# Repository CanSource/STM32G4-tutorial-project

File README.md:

# kicad project STM32G4-tutorial-project

a cool table showing the workflow of all the kicad projects.
| project_name | DRC | ERC |
| ------------ | --- | --- |
| stm32-tutorial-project | [❌](https://github.com/CanSource/STM32G4-tutorial-project/actions/runs/15577171902/attempts/1#summary-43864188891)| [❌](https://github.com/CanSource/STM32G4-tutorial-project/actions/runs/15577171902/attempts/1#summary-43864188888) | 

for a quick guide check [project setup](#project-setup)

This is a simple project template for new kicad projects. This template has some basic setup already completed such as workflows for auto creating all the things you forget when creating a kicad project such as:

- [gerbers](https://github.com/CanSource/STM32G4-tutorial-project/tree/main/stm32-tutorial-project_gerber.zip)
- [bom](https://github.com/CanSource/STM32G4-tutorial-project/tree/main/stm32-tutorial-project_bom_report.md)
- [schematic pdf](https://github.com/CanSource/STM32G4-tutorial-project/tree/main/stm32-tutorial-project_schematic.pdf)

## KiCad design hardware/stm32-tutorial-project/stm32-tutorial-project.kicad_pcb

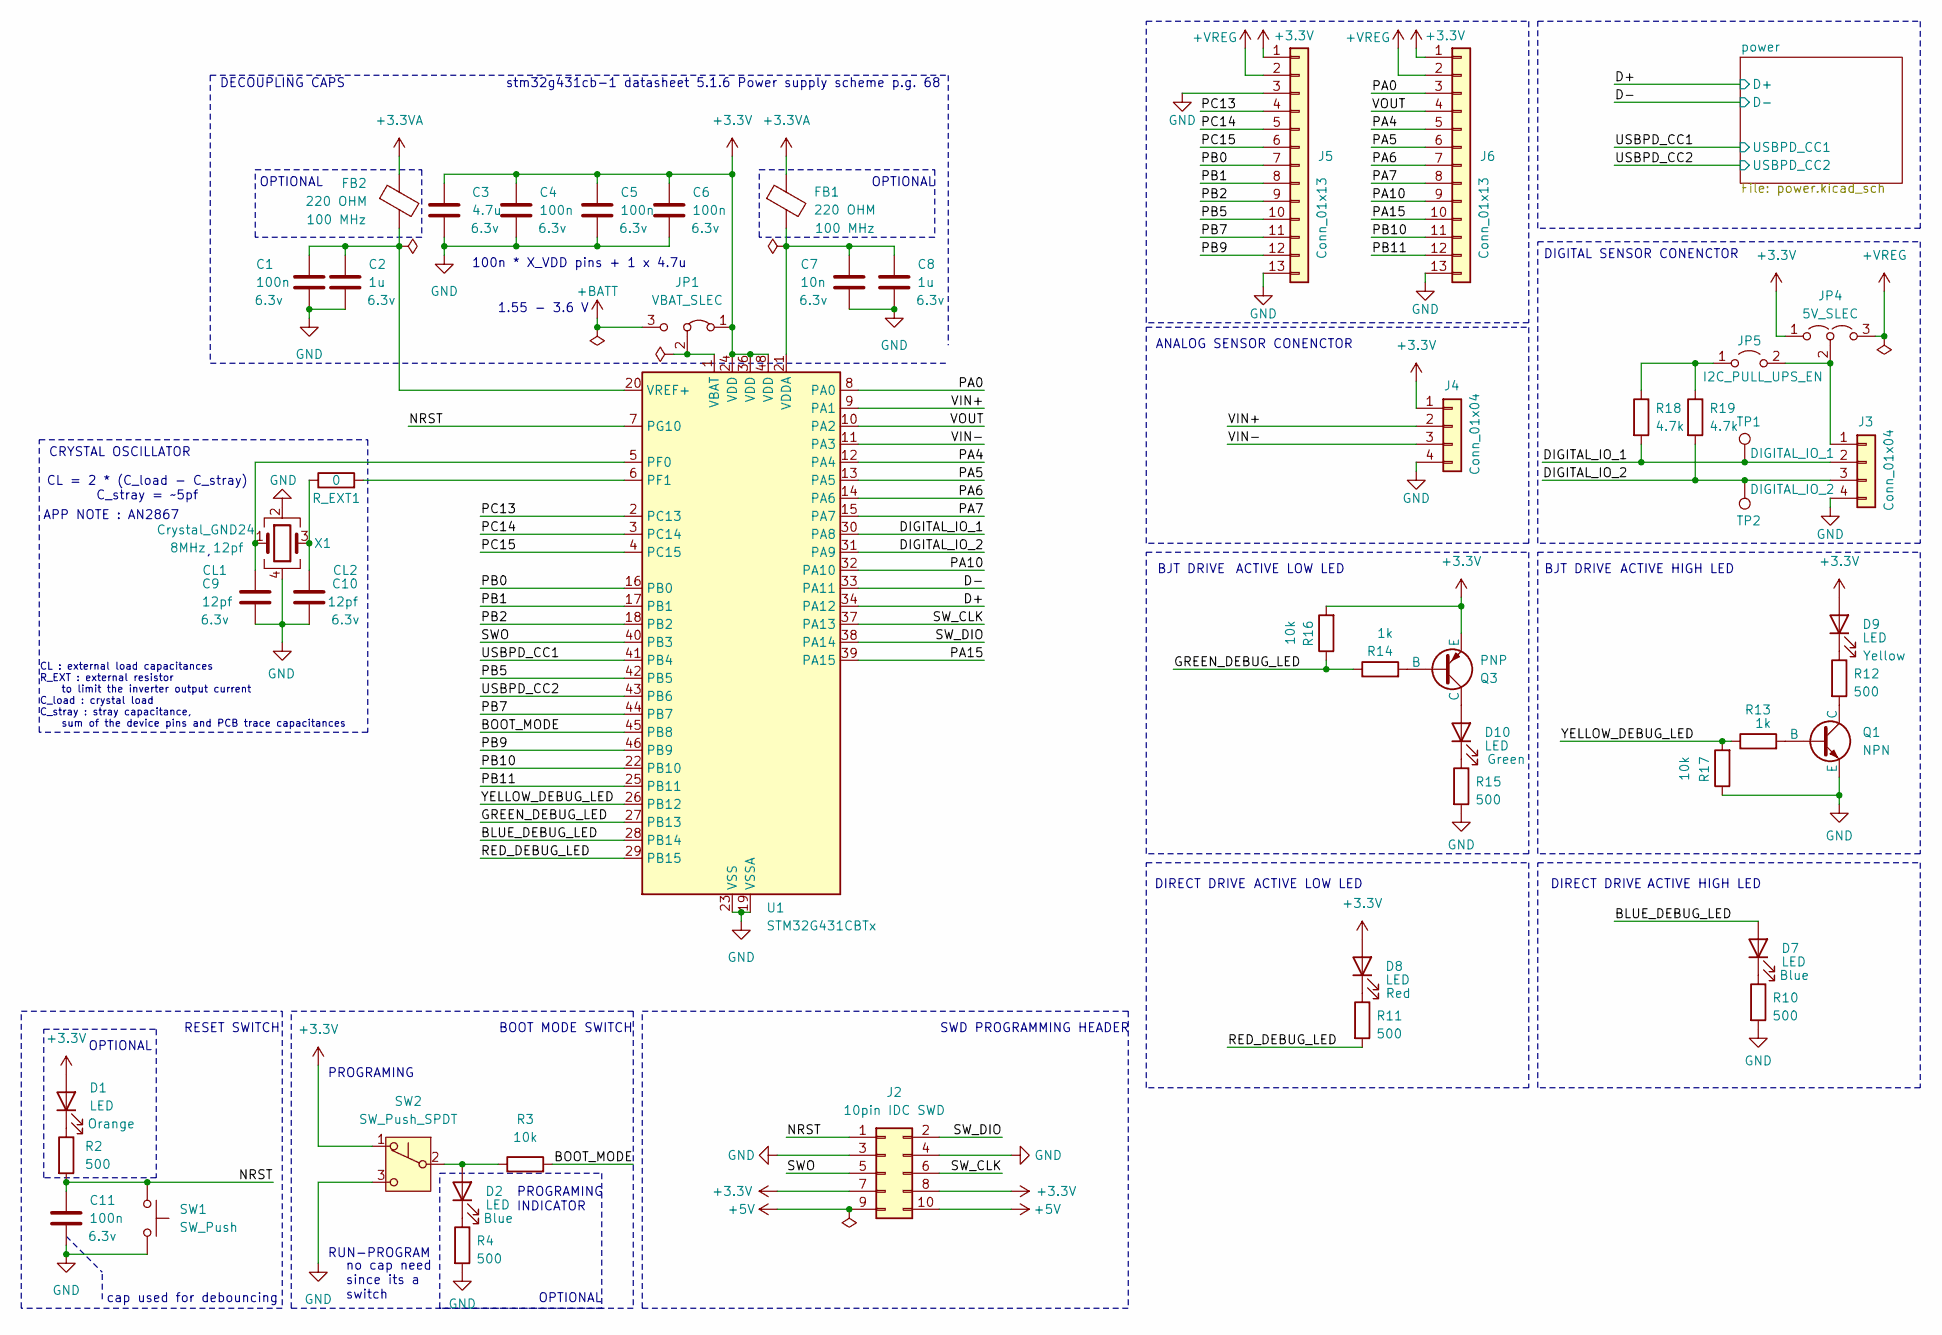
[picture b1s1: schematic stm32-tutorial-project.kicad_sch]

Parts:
C1: 100n; C_0603_1608Metric_Pad1.08x0.95mm_HandSolder; voltage 6.3v; rating X7R; Part Number C0603C104K9RACTU
C2, C8: 1u; C_0603_1608Metric_Pad1.08x0.95mm_HandSolder; voltage 6.3v; rating X7R; Part Number C0603C105K9RACTU
C3: 4.7u; C_0603_1608Metric_Pad1.08x0.95mm_HandSolder; voltage 6.3v; rating X5R; Part Number C0603C475K9PACTU
C4, C5, C6, C11: 100n; C_0603_1608Metric_Pad1.08x0.95mm_HandSolder; voltage 6.3v; rating X5R; Part Number C0603C104K9PACTU
C7: 10n; C_0603_1608Metric_Pad1.08x0.95mm_HandSolder; voltage 6.3v; rating X7R; Part Number C0603C103K9RACTU
C9, C10: 12pf; C_0603_1608Metric_Pad1.08x0.95mm_HandSolder; voltage 6.3v; rating X7R; Part Number C0603C120K9RAC7411
D1: LED; D_0603_1608Metric_Pad1.05x0.95mm_HandSolder; Part Number 150060AS75000
D2, D7: LED; D_0603_1608Metric_Pad1.05x0.95mm_HandSolder; Part Number 150060BS75000
D8: LED; D_0603_1608Metric_Pad1.05x0.95mm_HandSolder; Part Number 150060RS75000
D9: LED; D_0603_1608Metric_Pad1.05x0.95mm_HandSolder; Part Number 150060YS75000
D10: LED; D_0603_1608Metric_Pad1.05x0.95mm_HandSolder; Part Number 150060VS75000
FB1, FB2: 220 OHM; L_0603_1608Metric_Pad1.05x0.95mm_HandSolder; Part Number MH1608-221Y
J2: 10pin IDC SWD; IDC-Header_2x05_P2.54mm_Vertical; Part Number AWHW2 10G-0202
J3, J4: Conn_01x04; PinHeader_1x04_P2.54mm_Vertical; Part Number 1-0401FBV0T
J5, J6: Conn_01x13; PinHeader_1x13_P2.54mm_Vertical
JP1: VBAT_SLEC; SolderJumper-3_P1.3mm_Open_Pad1.0x1.5mm_NumberLabels
JP4: 5V_SLEC; PinHeader_1x03_P2.54mm_Vertical
JP5: I2C_PULL_UPS_EN; PinHeader_1x02_P2.54mm_Vertical
Q1: NPN; TSOT-23_HandSoldering; Part Number MMBT3904
Q3: PNP; TSOT-23_HandSoldering; Part Number MMBT3906
R2, R4, R10, R11, R12, R15: 500; R_0603_1608Metric_Pad0.98x0.95mm_HandSolder; Part Number RT0603BRD07500RL
R3, R16, R17: 10k; R_0603_1608Metric_Pad0.98x0.95mm_HandSolder; Part Number RC0603FR-0710KL
R13, R14: 1k; R_0603_1608Metric_Pad0.98x0.95mm_HandSolder; Part Number RC0603FR-0710KL
R18, R19: 4.7k; R_0603_1608Metric_Pad0.98x0.95mm_HandSolder; Part Number RC0603FR-074K7L
R_EXT1: 0; R_0603_1608Metric_Pad0.98x0.95mm_HandSolder; Part Number RC0603JR-070RL
SW1: SW_Push; SW_Tactile_SPST_NO_Straight_CK_PTS636Sx25SMTRLFS; Part Number PTS636SM43SMTR LFS
SW2: SW_Push_SPDT; SW_Slide_SPDT_Angled_CK_OS102011MA1Q; Part Number OS102011MA1QN1
TP1: DIGITAL_IO_1; TestPoint_Pad_D3.0mm
TP2: DIGITAL_IO_2; TestPoint_Pad_D3.0mm
U1: STM32G431CBTx; LQFP-48_7x7mm_P0.5mm; Part Number STM32G431CBT6
X1: Crystal_GND24; Crystal_SMD_3225-4Pin_3.2x2.5mm_HandSoldering; Part Number 12.60049

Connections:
+3.3V: C3.1, C4.1, C5.1, C6.1, D1.2 (A), D8.2 (A), D9.2 (A), FB1.1, FB2.1, J2.7, J2.8, J4.1, J5.1, J6.1, JP1.1 (A), JP4.1 (A), Q3.3 (E), R16.2, SW2.1 (A), U1.24 (VDD), U1.36 (VDD), U1.48 (VDD); also elsewhere on the board
+5V: J2.9, J2.10; also elsewhere on the board
+BATT: JP1.3 (B)
+VREG: J5.2, J6.2, JP4.3 (B); also elsewhere on the board
/BLUE_DEBUG_LED: D7.2 (A), U1.28 (PB14)
/BOOT_MODE: R3.2, U1.45 (PB8)
/D+: U1.34 (PA12); also elsewhere on the board
/D-: U1.33 (PA11); also elsewhere on the board
/DIGITAL_IO_1: J3.2, R18.2, TP1.1, U1.30 (PA8)
/DIGITAL_IO_2: J3.3, R19.2, TP2.1, U1.31 (PA9)
/GREEN_DEBUG_LED: R14.1, R16.1, U1.27 (PB13)
/NRST: C11.1, J2.1, R2.2, SW1.1, U1.7 (PG10)
/PA0: J6.3, U1.8 (PA0)
/PA4: J6.5, U1.12 (PA4)
/PA5: J6.6, U1.13 (PA5)
/PA6: J6.7, U1.14 (PA6)
/PA7: J6.8, U1.15 (PA7)
/PA10: J6.9, U1.32 (PA10)
/PA15: J6.10, U1.39 (PA15)
/PB0: J5.7, U1.16 (PB0)
/PB1: J5.8, U1.17 (PB1)
/PB2: J5.9, U1.18 (PB2)
/PB5: J5.10, U1.42 (PB5)
/PB7: J5.11, U1.44 (PB7)
/PB9: J5.12, U1.46 (PB9)
/PB10: J6.11, U1.22 (PB10)
/PB11: J6.12, U1.25 (PB11)
/PC13: J5.4, U1.2 (PC13)
/PC14: J5.5, U1.3 (PC14)
/PC15: J5.6, U1.4 (PC15)
/RED_DEBUG_LED: R11.2, U1.29 (PB15)
/SWO: J2.5, U1.40 (PB3)
/SW_CLK: J2.6, U1.37 (PA13)
/SW_DIO: J2.2, U1.38 (PA14)
/USBPD_CC1: U1.41 (PB4); also elsewhere on the board
/USBPD_CC2: U1.43 (PB6); also elsewhere on the board
/VIN+: J4.2, U1.9 (PA1)
/VIN-: J4.3, U1.11 (PA3)
/VOUT: J6.4, U1.10 (PA2)
/YELLOW_DEBUG_LED: R13.1, R17.2, U1.26 (PB12)
GND: C1.2, C2.2, C3.2, C4.2, C5.2, C6.2, C7.2, C8.2, C9.2, C10.1, C11.2, J2.3, J2.4, J3.4, J4.4, J5.3, J5.13, J6.13, Q1.3 (E), R4.2, R10.2, R15.2, R17.1, SW1.2, SW2.3 (C), U1.19 (VSSA), U1.23 (VSS), U1.35 (VSS), U1.47 (VSS), X1.2, X1.4; also elsewhere on the board
unnamed: C10.2, R_EXT1.1, X1.3
unnamed: D1.1 (K), R2.1
unnamed: D2.2 (A), R3.1, SW2.2 (B)
unnamed: D2.1 (K), R4.1
unnamed: D7.1 (K), R10.1
unnamed: D8.1 (K), R11.1
unnamed: D9.1 (K), R12.1
unnamed: D10.2 (A), Q3.1 (C)
unnamed: D10.1 (K), R15.1
unnamed: J3.1, JP4.2 (C), JP5.2 (B)
unnamed: JP1.2 (C), U1.1 (VBAT)
unnamed: JP5.1 (A), R18.1, R19.1
unnamed: Q1.2 (B), R13.2
unnamed: Q1.1 (C), R12.2
unnamed: Q3.2 (B), R14.2
unnamed: C9.1, U1.5 (PF0), X1.1
unnamed: R_EXT1.2, U1.6 (PF1)
unnamed: C7.1, C8.1, FB1.2, U1.21 (VDDA)
unnamed: C1.1, C2.1, FB2.2, U1.20 (VREF+)

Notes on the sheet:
DIGITAL SENSOR CONENCTOR
APP NOTE : AN2867
no cap need since its a switch
CRYSTAL OSCILLATOR
DECOUPLING CAPS
ACTIVE LOW LED
100n * X_VDD pins + 1 x 4.7u
cap used for debouncing
PROGRAMING INDICATOR
stm32g431cb-1 datasheet 5.1.6 Power supply scheme p.g. 68
RESET SWITCH
BJT DRIVE
ACTIVE HIGH LED
ANALOG SENSOR CONENCTOR
PROGRAMING
DIRECT DRIVE
OPTIONAL
1.55 - 3.6 V
RUN-PROGRAM
CL : external load capacitances R_EXT : external resistor to limit the inverter output current C_load : crystal load C_stray : stray capacitance, sum of the device pins and PCB trace capacitances
CL = 2 * (C_load - C_stray) C_stray = ~5pf
BOOT MODE SWITCH
SWD PROGRAMMING HEADER

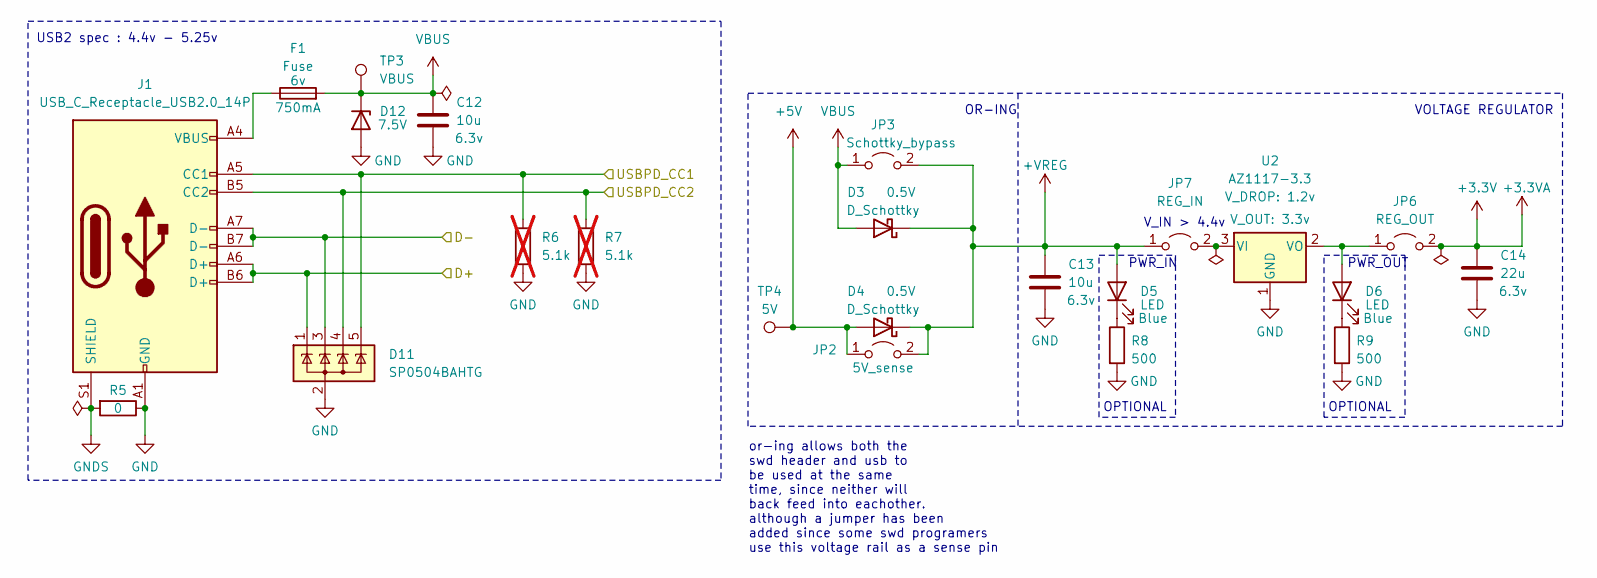
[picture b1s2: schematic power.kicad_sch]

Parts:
C12, C13: 10u; C_0603_1608Metric_Pad1.08x0.95mm_HandSolder; voltage 6.3v; rating X5R; Part Number C0603C106M9PACTU
C14: 22u; C_0603_1608Metric_Pad1.08x0.95mm_HandSolder; voltage 6.3v; rating X5R; Part Number C0805C226M9PACTU
D3, D4: D_Schottky; D_0603_1608Metric_Pad1.05x0.95mm_HandSolder; Part Number SD0805S020S1R0
D5, D6: LED; D_0603_1608Metric_Pad1.05x0.95mm_HandSolder; Part Number 150060BS75000
D11: SP0504BAHTG; SOT-23-5; Part Number SP0504BAHTG
D12: PTVS7V5Z1USK; Nexperia_DSN1608-2_1.6x0.8mm; Part Number PTVS7V5Z1USKYL
F1: Fuse; Fuse_0805_2012Metric; voltage 6v; Part Number 0ZCK0075FF2E
J1: USB_C_Receptacle_USB2.0_14P; USB_C_Receptacle_HRO_TYPE-C-31-M-12; Part Number USB4105-GF-A
JP2: 5V_sense; SolderJumper-2_P1.3mm_Open_Pad1.0x1.5mm
JP3: Schottky_bypass; SolderJumper-2_P1.3mm_Open_Pad1.0x1.5mm
JP6: REG_OUT; SolderJumper-2_P1.3mm_Open_Pad1.0x1.5mm
JP7: REG_IN; SolderJumper-2_P1.3mm_Open_Pad1.0x1.5mm
R5: 0; R_0603_1608Metric_Pad0.98x0.95mm_HandSolder; Part Number RC0603JR-070RL
R6, R7: 5.1k; R_0603_1608Metric_Pad0.98x0.95mm_HandSolder; Part Number RC0603FR-075K1L; not fitted
R8, R9: 500; R_0603_1608Metric_Pad0.98x0.95mm_HandSolder; Part Number RT0603BRD07500RL
TP3: VBUS; TestPoint_Pad_D3.0mm
TP4: 5V; TestPoint_Pad_D3.0mm
U2: AZ1117-3.3; SOT-223-3_TabPin2; Part Number AZ1117CH-3.3TRG1

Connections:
+3.3V: C14.1, JP6.2 (B); also elsewhere on the board
+5V: D4.2 (A), JP2.1 (A), TP4.1; also elsewhere on the board
+VREG: C13.1, D3.1 (K), D4.1 (K), D5.2 (A), JP2.2 (B), JP3.2 (B), JP7.1 (A); also elsewhere on the board
/D+: D11.1 (K), J1.A6 (D+), J1.B6 (D+); also elsewhere on the board
/D-: D11.3 (K), J1.A7 (D-), J1.B7 (D-); also elsewhere on the board
/USBPD_CC1: D11.5 (K), J1.A5 (CC1), R6.1; also elsewhere on the board
/USBPD_CC2: D11.4 (K), J1.B5 (CC2), R7.1; also elsewhere on the board
GND: C12.2, C13.2, C14.2, D11.2 (A), D12.2 (A), J1.A1 (GND), J1.A12 (GND), J1.B1 (GND), J1.B12 (GND), R5.1, R6.2, R7.2, R8.2, R9.2, U2.1 (GND); also elsewhere on the board
GNDS: J1.S1 (SHIELD), R5.2
unnamed: D5.1 (K), R8.1
unnamed: D6.2 (A), JP6.1 (A), U2.2 (VO)
unnamed: D6.1 (K), R9.1
unnamed: F1.1, J1.A4 (VBUS), J1.A9 (VBUS), J1.B4 (VBUS), J1.B9 (VBUS)
unnamed: JP7.2 (B), U2.3 (VI)
VBUS: C12.1, D3.2 (A), D12.1 (K), F1.2, JP3.1 (A), TP3.1

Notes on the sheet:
V_IN > 4.4v
OPTIONAL
USB2 spec : 4.4v - 5.25v
PWR_IN
or-ing allows both the swd header and usb to be used at the same time, since neither will back feed into eachother. although a jumper has been added since some swd programers use this voltage rail as a sense pin
VOLTAGE REGULATOR
PWR_OUT
OR-ING

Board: 2 copper layers, 72 parts (0 on the bottom side), 66 nets, no tracks yet.

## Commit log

2025-03-19 added workflow
2025-03-19 ignore all the unnecessary auto created kicad file
2025-03-19 added CERN Open Hardware Licence
2025-03-19 added project settings for github actions
2025-03-19 start of tutorial
2025-03-19 getting rid of the .lck file
2025-03-19 added .lck to ignore list
2025-03-19 added mcu
2025-03-19 auto update
2025-03-19 added dir for github action outputs
2025-03-21 removed un-needed settings
2025-03-21 article structre notes
2025-03-21 added stm32g4 to schmatic
2025-03-21 updated note to follow a new layout
2025-03-21 added notes on power supply design
2025-03-21 added decoupling caps to mcu
2025-03-21 added hash to notes
2025-03-21 added crystal to schmatic
2025-03-21 added crystal to notes
2025-03-22 added ferrite beads to analog power
2025-03-22 added notes on beads
2025-03-22 added hash to section
2025-03-22 added reset button
2025-03-22 added notes on reset button
2025-03-22 added boot mode switch
2025-03-22 added programming header
2025-03-22 added programming notes and hashes
2025-03-22 added usb port to pcb
2025-03-22 added notes on usb c
2025-03-22 added usb hash
2025-03-22 added hierarchically sheet for power
2025-03-22 moved usb c into hierarchically sheet
2025-03-22 added voltage regulator to hierarchically sheet
2025-03-22 added power hash to notes
2025-03-23 updated power circuit with more info on or-ing circuit voltags and added status leds
2025-03-23 added more info to power notes
2025-03-23 added debug leds
2025-03-23 added some notes on leds but no where near enough yet
2025-03-23 supplier links to comps, will be added to the schematic later, in a further step
2025-03-23 production files
2025-03-25 added connectors for distance sensors
2025-03-25 added leds
2025-03-25 added notes aobut distance sensors
2025-03-25 added docs about pin headers
2025-03-25 added esd diodes
2025-03-25 added connectors for extra pins
2025-03-27 fixed leds and added debug leds to stm32 pins oops
2025-04-04 added fuse to power input
2025-04-04 add buttons, diode and transistors
2025-04-04 added some eqs around fuses
2025-04-04 added testpoints
2025-04-04 added notes on testpoints and jumpers
2025-04-04 erc should be fixed now
2025-04-04 please tell me this fixed erc
2025-04-05 added notes and moved links to the sch
2025-04-05 added supplier links, part numbers and datasheets
2025-04-05 digikart as a .csv file incase the link breaks
2025-04-05 start of the pcb
2025-04-05 added part number supplier link and datasheets to the bom
2025-04-05 added user gen BOM since i dont trust the action will output everything
2025-04-10 added footprints to the jumpers
2025-04-10 added footprints to jumpers and footprints to pin headers
2025-04-10 removed anything in it to start anew
2025-04-10 Role over to KiCAD 9, prep for PCB layout
2025-04-10 Correct PNP LED driver to match NPN behaviour per #1
2025-04-10 updated action to allow for kicad 9 to be used
2025-04-10 updated to kicad 9
2025-04-10 Add missing connectors, test points, and jumpers
2025-04-10 Correct remaining connectors, complete ratsnest now available
2025-04-10 Break ratsnest into functional sections
2025-04-10 Begin iteration on USB connection/regulator path
2025-05-14 updated sparkengineering/kicad-action@v3 to sparkengineering/kicad-action@v4 to support kicad 9
2025-05-14 removed backtick
2025-06-11 added notes on the usbpd circuit
2025-06-11 now shows part number for the tvs diode
2025-06-11 added dead battery pins to the cc lines so usbpd will work correctly
